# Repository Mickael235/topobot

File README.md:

# TopoBot

<p align="center">
  <strong>Autonomous holonomic robot for automated topographic surface-flatness inspection</strong><br>
  ENSIM × ESGT · 4th-year Engineering Project · 20252026
</p>

<p align="center">
  <strong>STM32 F446RE · Raspberry Pi · Mecanum · Encoders · AX-12 · XBee · KiCad · Python · C</strong>
</p>

---

## Project overview

**TopoBot** is a holonomic mobile robot developed to automate the repetitive part of a topographic surface-flatness survey.

In a conventional workflow, an operator manually moves a reflector from point to point while another operator operates the total station. TopoBot was designed to replace this manual point-by-point displacement with a configurable robotic mission:

1. define the measurement grid;
2. navigate to each waypoint;
3. deploy the topographic prism;
4. trigger / acquire the measurement;
5. recover the coordinates;
6. store and export the results.

The project combines **robotics, embedded control, electronics, radio communication, software supervision and topographic instrumentation** in one integrated prototype.

> **Project status:** the main hardware/software building blocks were integrated and validated on the prototype. Final industrial-grade accuracy, complete odometry/total-station fusion and a full production flatness campaign remain future work.

---

## Project at a glance

| Item | Implementation |
|---|---|
| Mobile base | Lynxmotion A4WD3 with 4 Mecanum wheels |
| Real-time controller | STM32 Nucleo F446RE |
| High-level computer | Raspberry Pi 4 |
| Motor power stage | 2 × Sabertooth motor drivers |
| Motion feedback | 4 incremental wheel encoders |
| Prism mechanism | AX-12 servomotor + rack-and-pinion mechanism |
| Station communication | XBee S2C radio link + serial / RS232 interface |
| Supervision | TopoBot Manager on tablet / browser |
| Data storage | SQLite on Raspberry Pi |
| Export | CSV |
| Real-time control loop | 100 Hz |
| Project budget | 500 |
| Actual project cost | 318.26 |
| Team | 4 engineering students |

### Design target

The functional specification targeted a configurable survey grid up to **50 m × 50 m**, with a nominal **0.5 m grid spacing** and a **40 mm spherical reflector**.

This is a **design requirement**, not a claim that the complete 50 × 50 m campaign was validated during the project.

---

# 1. Problem and mission

Manual surface inspection with a total station is repetitive: the reflector must be moved and positioned at many points, while measurements are triggered and recorded.

TopoBot aims to transform this workflow into a supervised autonomous sequence.

## Nominal survey cycle

```text
Define grid
    ?
Generate waypoints
    ?
Navigate to waypoint
    ?
Stabilize robot
    ?
Deploy prism
    ?
Trigger total-station measurement
    ?
Recover XYZ / angles / distance
    ?
Retract prism
    ?
Store point in SQLite
    ?
Send progress to TopoBot Manager
    ?
Next waypoint
    ?
Export mission data to CSV
```

The trajectory is generated as a **boustrophedon path**: the direction alternates from one grid row to the next to reduce unnecessary travel.

---

# 2. Functional architecture

The robot must interact with the surveyor, the surface, the total station, the energy source and the safety environment.

The main service functions are:

| Ref. | Function | Main requirement |
|---|---|---|
| FP1 | Move and orient the reflector | Configurable grid, 40 mm reflector |
| FC1 | Communicate with the total station | XBee S2C radio link, commands + coordinates |
| FC2 | Provide configuration and monitoring | Tablet / smartphone interface |
| FC3 | Provide energy autonomy | Rechargeable battery |
| FC4 | Operate in an indoor environment | Flat surface, future obstacle/drop detection |
| FC5 | Respect safety/environment constraints | Emergency stop and safe integration |

---

# 3. Robot structure

TopoBot is not a single-controller robot. It uses a **distributed architecture** in which the computational responsibilities are separated.

## Three control levels

```mermaid
flowchart LR
    UI["Tablet / Browser<br><b>TopoBot Manager</b>"]
    PI["Raspberry Pi 4<br><b>Mission supervisor / middleware</b>"]
    MCU["STM32 F446RE<br><b>Real-time motion controller</b>"]

    UI <-->|Network / Web interface| PI
    PI <-->|Binary serial protocol| MCU
```

### Level 1  Tablet / front-end

The operator uses TopoBot Manager to:

- connect to the robot;
- configure the survey area;
- choose the grid spacing;
- initialize the measurement mode;
- launch the mission;
- monitor progress;
- read logs and telemetry;
- stop the robot;
- export results.

### Level 2  Raspberry Pi / middleware

The Raspberry Pi acts as the high-level computer. It is responsible for:

- mission generation;
- waypoint sequencing;
- communication with the STM32;
- communication with the total station;
- measurement orchestration;
- SQLite data storage;
- WebSocket progress updates;
- CSV export;
- serving the supervision application.

### Level 3  STM32 / real-time control

The STM32 F446RE performs the time-critical functions:

- encoder acquisition;
- odometry;
- motion state machine;
- closed-loop motor control;
- Sabertooth command generation;
- emergency-stop handling;
- AX-12 prism control;
- execution of high-level motion orders.

This separation keeps real-time control local to the microcontroller while the Raspberry Pi focuses on supervision and mission logic.

---

# 4. Complete hardware architecture

```mermaid
flowchart TD
    APP["TopoBot Manager<br>Tablet / PC"]
    RPI["Raspberry Pi 4<br>Mission supervisor"]
    STM["STM32 F446RE<br>100 Hz real-time control"]
    PCB["Custom control board<br>KiCad / JLCPCB"]

    ENC["4 wheel encoders"]
    SAB["2 × Sabertooth<br>motor drivers"]
    MOT["4 DC motors<br>4 Mecanum wheels"]
    AX["AX-12 servo<br>Prism deployment"]
    ESTOP["Emergency stop"]
    BATT["Battery monitoring"]

    XB1["XBee S2C #1"]
    XB2["XBee S2C #2"]
    RS232["MAX3232 / RS232"]
    TOPCON["Robotic total station"]

    APP <-->|Supervision| RPI
    RPI <-->|Binary serial protocol| STM

    ENC --> STM
    STM --> PCB
    PCB --> SAB
    SAB --> MOT
    STM --> AX
    ESTOP --> PCB
    BATT --> PCB

    RPI <-->|USB / UART serial| XB1
    XB1 <-. "Radio" .-> XB2
    XB2 <-->|Serial| RS232
    RS232 <-->|RS232| TOPCON
```

---

# 5. Holonomic Mecanum platform

The Lynxmotion A4WD3 base uses four Mecanum wheels, allowing longitudinal, lateral and rotational motion.

## Wheel-direction combinations

| Motion | Front Left | Front Right | Rear Left | Rear Right |
|---|---:|---:|---:|---:|
| Forward | + | + | + | + |
| Backward | - | - | - | - |
| Left translation | - | + | + | - |
| Right translation | + | - | - | + |
| Left rotation | - | + | - | + |
| Right rotation | + | - | + | - |

The current survey mission mainly uses **translations with a constant orientation**. Nevertheless, the command interface preserves the full pose parameter:

```text
MOVE_TO(x, y, theta)
```

This keeps the architecture extensible toward complete pose control.

## Physical testing

Early tests demonstrated the expected Mecanum motion but also revealed parasitic rotation during straight translations due to wheel/motor asymmetry.

This led to:

- individual wheel testing;
- lower-speed validation;
- exploitation of encoder feedback;
- progressive closed-loop tuning.

---

# 6. STM32 real-time control

The embedded firmware is organised around several modules:

```text
STM32 firmware
+-- Mecanum kinematics
+-- Encoder acquisition
+-- Odometry
+-- PID / motion control
+-- Robot state machine
+-- Raspberry Pi protocol
+-- AX-12 prism control
+-- Safety / robot configuration
```

The repository contains the STM32 project in:

```text
firmware/stm32/
```

## Robot state machine

The controller uses the following main states:

```mermaid
stateDiagram-v2
    [*] --> IDLE
    IDLE --> MOVING: MOVE_TO
    MOVING --> SETTLING: target reached
    SETTLING --> DONE: position confirmed
    DONE --> IDLE
    MOVING --> ERROR: fault
    SETTLING --> ERROR: fault
    IDLE --> ESTOP: emergency stop
    MOVING --> ESTOP: emergency stop
    SETTLING --> ESTOP: emergency stop
```

Main states:

- `IDLE`  waiting for a command;
- `MOVING`  moving toward the target;
- `SETTLING`  stabilizing around the waypoint;
- `DONE`  waypoint reached and confirmed;
- `ERROR` / `ESTOP`  error or emergency stop.

The Raspberry Pi only sends the next waypoint after receiving a `DONE` status.

---

# 7. Raspberry Pi ? STM32 protocol

The Raspberry Pi does not directly control the motors.

It sends high-level commands to the STM32 using a lightweight binary protocol:

```text
[ START | CMD | LEN | PAYLOAD | CRC ]
```

The project uses a simple XOR-based CRC over the command, payload length and payload.

## Main commands

| Command | Role |
|---|---|
| `MOVE_TO` | Reach target pose `(x, y, ?)` |
| `STOP` | Immediate robot stop |
| `RESET_ODOM` | Reset odometry before a mission |
| `GET_STATUS` | Read position, speed and current state |
| `DEPLOY_PRISM` | Deploy the topographic prism |
| `RETRACT_PRISM` | Retract the prism |

The STM32 returns status frames such as:

```text
STATUS
DONE
ERROR
```

These messages allow the Raspberry Pi backend to orchestrate the mission without interfering with the real-time control loop.

---

# 8. Automatic mission logic

The mission is generated from:

```text
Zone width  = X
Zone length = Y
Grid step   = p
```

The backend generates the waypoint set:

```text
(xi, yj)
xi = i × p
yj = j × p
```

and orders them in a boustrophedon trajectory.

## Exact mission order

```text
1. RESET_ODOM
   +- Reset the robot local reference before starting.

2. Generate waypoints
   +- Build the complete boustrophedon measurement grid.

3. For each waypoint:
   +- Send MOVE_TO(x, y, ?)
   +- Wait for STM32 STATUS updates
   +- Continue only after DONE

4. If measurement mode is enabled:
   +- DEPLOY_PRISM
   +- Trigger / request Topcon measurement
   +- Recover measurement values
   +- RETRACT_PRISM

5. Save measurement
   +- Timestamp + local coordinates + station data ? SQLite

6. Notify front-end
   +- Mission progress and current data ? WebSocket

7. Continue with next waypoint

8. End mission
   +- Export the recorded dataset to CSV
```

A **station-independent test mode** was also kept. In this mode the robot can execute the grid with simulated measurement values, making it possible to debug navigation without depending on the topographic instrument.

---

# 9. Prism deployment mechanism

The topographic reflector is mounted on a rack-and-pinion mechanism actuated by an **AX-12 servomotor**.

The mechanism is responsible for:

```text
RETRACTED
    ?
DEPLOY_PRISM
    ?
Prism positioned for measurement
    ?
Total-station acquisition
    ?
RETRACT_PRISM
    ?
Robot resumes navigation
```

This sequence is synchronized with waypoint validation so that measurements are not requested while the robot is still moving.

---

# 10. Custom electronics

A custom control board was designed in **KiCad**, manufactured by **JLCPCB**, assembled and integrated into the robot.

The control electronics centralize:

- four encoder interfaces;
- STM32 connectivity;
- Sabertooth motor-control connections;
- AX-12 interface;
- emergency-stop circuitry;
- centralized power management;
- analog battery monitoring;
- expansion ports for future ultrasonic sensors.

The pre-existing power board was reused, while the **control board was redesigned specifically for this project**.

The KiCad project and Gerber manufacturing files are available under:

```text
hardware/control-board/
+-- kicad/
+-- manufacturing/
    +-- gerbers/
```

---

# 11. XBee radio link and total-station interface

TopoBot communicates with the robotic total station through a dedicated radio/serial chain.

## Communication chain

```text
Raspberry Pi
    ¦
    ¦ USB / UART serial
    ?
XBee S2C #1
    ))) RADIO (((
XBee S2C #2
    ¦
    ¦ Serial
    ?
MAX3232 / RS232 converter
    ¦
    ¦ RS232
    ?
Robotic total station
```

## XBee configuration used during the project

| Parameter | Configuration |
|---|---|
| Baud rate | 9600 |
| Data bits | 8 |
| Parity | None |
| Stop bits | 1 |
| Flow control | None |
| Channel | `C` / `0x0C` |
| PAN ID | `B332` |

The modules were configured using **Digi XCTU**.

## Total-station operating modes

The project explored three main station modes:

### Standard (`std`)
High-precision fixed measurement using fine targeting.

### Tracking (`trk`)
Fast tracking / targeting of a moving reflector.

### Continuous tracking
Continuous acquisition of distances and horizontal/vertical angles.

The automated acquisition sequence uses the station together with the robot prism workflow to recover the current measured point and feed it back into the mission data.

> **Known limitation:** the XBee radio link showed intermittent reliability problems during field testing. Improving the radio layer is one of the main future-work items.

---

# 12. TopoBot Manager

**TopoBot Manager** is the supervision interface designed for tablet use.

Its purpose is to hide the complexity of the robot, STM32, Raspberry Pi and total station behind a guided workflow.

The application follows three main user stages.

## 01  Connection

Before a mission starts, the interface verifies that the robot and measurement system are reachable.

Typical checks include:

- robot / Raspberry Pi connectivity;
- total-station link state;
- initialization readiness.

The operator cannot proceed until the system is ready.

## 02  Mission configuration

The operator defines:

- survey width `X`;
- survey length `Y`;
- measurement step `p`;
- measurement mode.

The backend uses these values to determine the grid and generate the mission waypoints.

## 03  Live mission supervision

During execution, the interface displays:

- mission progress;
- current point;
- 2D map of the grid;
- robot position;
- completed measurement points;
- activity/event log;
- latest measurement values;
- radio / system information;
- emergency-stop action.

---

# 13. Software communication layers

The complete information flow can be summarized as:

```text
+--------------------------------------+
¦ Tablet / Browser                    ¦
¦ TopoBot Manager                     ¦
¦ - configuration                     ¦
¦ - live map                          ¦
¦ - progress                          ¦
¦ - logs                              ¦
¦ - emergency stop                    ¦
+--------------------------------------+
                    ¦ HTTP / WebSocket
                    ?
+--------------------------------------+
¦ Raspberry Pi                        ¦
¦ Middleware / Mission Supervisor     ¦
¦ - route generation                  ¦
¦ - waypoint orchestration            ¦
¦ - SQLite                            ¦
¦ - CSV export                        ¦
¦ - total-station communication       ¦
+--------------------------------------+
                ¦               ¦
        Binary serial           ¦ XBee / serial
                ¦               ¦
                ?               ?
+----------------------+   +---------------------+
¦ STM32 F446RE         ¦   ¦ Robotic total      ¦
¦ - odometry           ¦   ¦ station            ¦
¦ - encoders           ¦   ¦ - measurement      ¦
¦ - PID                ¦   ¦ - tracking         ¦
¦ - motors             ¦   ¦ - XYZ / angles     ¦
¦ - AX-12              ¦   +---------------------+
+----------------------+
```

---

# 14. Data acquisition and export

Each measurement point is stored locally on the Raspberry Pi.

The project uses **SQLite** for mission data and exposes the final dataset through **CSV export**.

## Recorded fields

| Field | Meaning |
|---|---|
| `ID` | Unique measurement-point identifier |
| `HEURE` | Acquisition timestamp |
| `X`, `Y` | Local planar coordinates |
| `HZ` | Horizontal station angle |
| `V` | Vertical station angle |
| `DIST` | Radial distance measured by the station |

The mission data lifecycle is:

```text
Connection
    ?
Geometry configuration
    ?
Survey supervision
    ?
SQLite storage
    ?
CSV export
```

The CSV format was chosen to keep the results directly usable in spreadsheets and topographic post-processing tools.

---

# 15. Validation

The project was developed using progressive integration and physical tests.

## Tests performed

- individual motor-direction tests;
- Mecanum wheel-combination tests;
- forward/backward translation;
- lateral translation;
- encoder acquisition;
- odometry;
- Raspberry Pi ? STM32 communication;
- high-level `MOVE_TO` commands;
- robot state-machine behavior;
- AX-12 prism deployment/retraction;
- XBee radio communication;
- total-station operating modes;
- TopoBot Manager connection/configuration/live monitoring;
- mission generation and waypoint sequencing;
- station-independent simulated-measurement mode.

## Current validation status

| Subsystem | Status |
|---|---|
| Mecanum basic motion | ? Validated |
| STM32 real-time architecture | ? Implemented |
| Encoder feedback / odometry | ? Integrated |
| Raspberry Pi ? STM32 protocol | ? Implemented |
| High-level waypoint mission logic | ? Implemented |
| AX-12 prism deployment | ? Integrated and validated |
| Custom control PCB | ? Designed, manufactured and assembled |
| TopoBot Manager | ? Functional |
| Total-station communication modes | ? Exercised |
| XBee field robustness | ?? Functional but unreliable in some tests |
| Closed-loop tuning | ?? Requires finer adjustment |
| Odometry + total-station fusion | ?? Future work |
| Complete production flatness campaign | ?? Still to be finalized |

The goal of this repository is to present the **real engineering state of the prototype**, including both validated subsystems and remaining technical limitations.

---

# 16. Engineering challenges encountered

## Wheel synchronization

The first physical tests revealed unwanted rotation during straight movement.

Probable causes included:

- different mechanical behavior between motors;
- left/right timing asymmetry;
- open-loop control limitations.

Encoder feedback and closed-loop control were introduced to improve trajectory stability.

## Odometry drift

Wheel odometry accumulates errors when the wheels slip or the ground is irregular.

A future version should fuse:

```text
Wheel odometry
      +
High-precision total-station coordinates
      ?
Corrected robot localization
```

## Radio robustness

The XBee solution proved useful for prototyping but showed intermittent signal losses.

A more robust professional radio solution would be preferable for field deployment.

## Wiring reliability

The prototype contains a significant amount of point-to-point wiring. A future revision should use:

- locking connectors;
- improved cable routing;
- additional functions integrated directly onto the PCB.

## Active safety

Obstacle/drop sensors were planned in the architecture but were not fully operational in the final prototype.

---

# 17. My contribution

This was a **four-person team project** with distinct technical work packages.

My contribution focused primarily on **control, kinematics and motion validation**, including:

- development and validation of robot movement behavior;
- Mecanum motion testing;
- trajectory-execution testing;
- analysis of encoder feedback and positioning errors;
- participation in odometry / motion-control integration;
- contribution to waypoint and mission-motion logic;
- integration and testing of the AX-12 prism mechanism;
- physical prototype testing and debugging.

The complete project also includes major contributions from the other team members in supervision/UI, XBee communication and electronics/PCB integration.

---

# 18. Team organization

| Team member | Main work package |
|---|---|
| Bénéwindé Kontiebo | Project management · Supervision · HMI |
| Aymane Fariss | Communication · XBee / total-station link |
| Arsène Nguenang Youkap | Electronics · PCB · hardware integration |
| **Michael Essomba** | **Control · kinematics · AX-12 prism mechanism** |

The project was managed using an agile-inspired workflow with regular synchronization and milestone reviews.

---

# 19. Budget and reuse strategy

The project operated under a **500 budget**.

| Metric | Value |
|---|---:|
| Available budget | 500 |
| Actual project cost | **318.26** |
| Remaining budget | 181.74 |
| Budget utilization | ~64% |

A significant part of the platform was reused from previous cohorts:

- Lynxmotion chassis;
- DC motors;
- Mecanum wheels;
- Sabertooth drivers;
- XBee modules;
- AX-12 servo;
- prism mechanism;
- existing power board.

New spending focused mainly on the Raspberry Pi, STM32 boards, control electronics, passive components and PCB manufacturing.

---

# 20. Repository structure

```text
topobot/
+-- README.md
+-- .gitignore
¦
+-- assets/
¦   +-- images/
¦   ¦   +-- hero/
¦   ¦   ¦   +-- topobot-hero.png
¦   ¦   ¦
¦   ¦   +-- diagrams/
¦   ¦   ¦   +-- functional-architecture.png
¦   ¦   ¦   +-- mission-workflow.png
¦   ¦   ¦   +-- xbee-communication-chain.png
¦   ¦   ¦
¦   ¦   +-- hardware/
¦   ¦   ¦   +-- robot-platform.png
¦   ¦   ¦   +-- control-and-power-board.png
¦   ¦   ¦   +-- total-station.png
¦   ¦   ¦   +-- robot-cad-render.png
¦   ¦   ¦
¦   ¦   +-- ui/
¦   ¦       +-- topobot-manager-flow.png
¦   ¦       +-- mission-config.png
¦   ¦       +-- mission-live-dashboard.png
¦   ¦
¦   +-- video/
¦       +-- topobot-demo.mp4
¦
+-- docs/
¦   +-- presentation/
¦   +-- report/
¦   +-- technical/
¦
+-- firmware/
¦   +-- stm32/
¦
+-- hardware/
¦   +-- control-board/
¦       +-- kicad/
¦       +-- manufacturing/
¦           +-- gerbers/
¦
+-- software/
    +-- raspberry-pi/
    ¦   +-- tests/
    ¦
    +-- topobot-manager/
        +-- backend/
        +-- frontend/
```

Generated build files, local databases, virtual environments, IDE temporary files and dependency directories are intentionally excluded from version control.

---

# 21. Technologies

### Embedded systems

`C` · `STM32 F446RE` · `STM32CubeIDE` · `HAL`

### Robotics and control

`Mecanum kinematics` · `Encoders` · `Odometry` · `PID` · `State machine` · `AX-12`

### High-level software

`Python` · `Raspberry Pi` · `SQLite` · `WebSocket`

### Communication

`UART` · `Serial` · `XBee S2C` · `RS232`

### Electronics

`KiCad` · `PCB design` · `Gerber` · `JLCPCB`

### Instrumentation

`Robotic total station` · `Topographic prism` · `Tracking`

### Development

`Git` · `GitHub` · `Hardware testing` · `Technical documentation`

---

# 22. Demo

A short demonstration of the physical prototype is available here:

### [? Watch the TopoBot demo](assets/video/topobot-demo.mp4)

---

# 23. Documentation

Detailed engineering documentation is available in [`docs/`](docs/).

Main documents:

- [Final project report](docs/report/Rapport_final.pdf)
- [Project presentation](docs/presentation/TopoBot_Presentation.pdf)
- [STM32 firmware documentation](docs/technical/firmware/)
- [Hardware and wiring documentation](docs/technical/hardware/)
- [Raspberry Pi documentation](docs/technical/raspberry-pi/)
- [Testing documentation](docs/technical/tests/)
- [Odometry, PID and validation documentation](docs/technical/advanced/)

---

# 24. Future work

The next engineering priorities are:

1. **PID tuning**  
   Reduce oscillations and trajectory error.

2. **Odometry calibration**  
   Improve the estimation of `x`, `y` and `?`.

3. **Odometry / total-station sensor fusion**  
   Correct wheel-slip drift using high-precision station feedback.

4. **Radio reliability**  
   Replace or harden the XBee communication chain for field use.

5. **Active navigation safety**  
   Integrate obstacle, drop and stair detection.

6. **Wiring redesign**  
   Reduce point-to-point wiring and use locking connectors.

7. **Large-grid validation**  
   Validate longer missions and repeated surveys under realistic conditions.

8. **Full flatness campaign**  
   Complete the end-to-end autonomous survey and compare results against a reference workflow.

---

# 25. Project outcome

TopoBot evolved from an inherited mechanical platform into an integrated robotic prototype combining:

- a redesigned embedded architecture;
- STM32 real-time motion control;
- Raspberry Pi mission supervision;
- custom control electronics;
- Mecanum mobility;
- encoder odometry;
- AX-12 prism deployment;
- XBee / total-station communication;
- tablet-based mission supervision;
- local measurement storage and CSV export.

The project demonstrates the feasibility of automating a topographic surface-inspection workflow while also identifying the engineering work still required to reach robust field deployment.

---

# Project team

**ENSIM × ESGT  Le Mans University**  
Academic year: **20252026**

- Bénéwindé Kontiebo
- **Michael Essomba**
- Arsène Nguenang Youkap
- Aymane Fariss

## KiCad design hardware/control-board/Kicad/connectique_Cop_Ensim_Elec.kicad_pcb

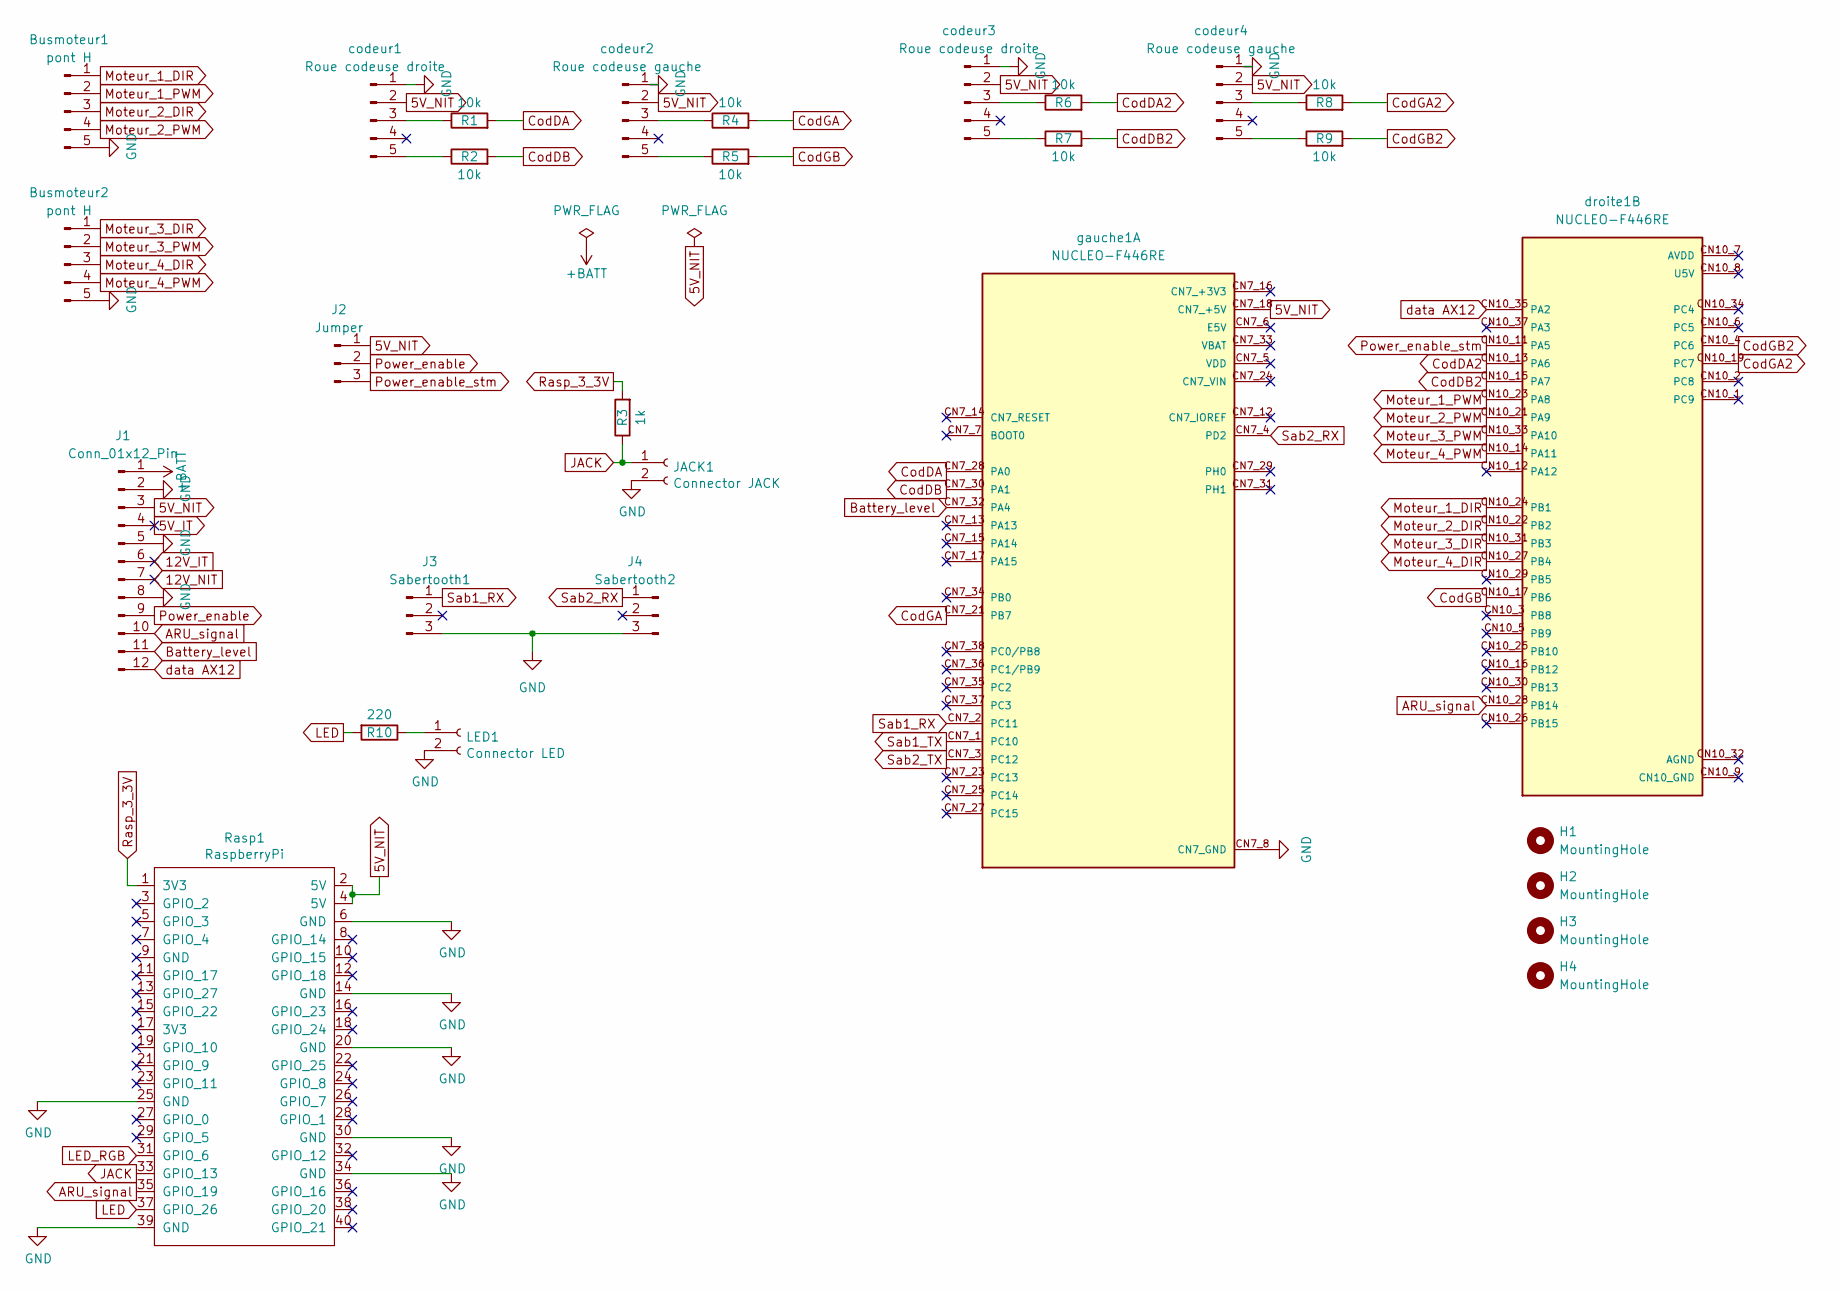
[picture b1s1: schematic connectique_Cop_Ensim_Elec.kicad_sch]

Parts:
Busmoteur1, Busmoteur2: pont H; JST_PH_B5B-PH-K_1x05_P2.00mm_Vertical
H1, H2, H3, H4: MountingHole; MountingHole_3.2mm_M3_DIN965_Pad
J1: Conn_01x12_Pin; PinHeader_1x12_P2.54mm_Vertical
J2: Jumper; PinHeader_1x03_P2.54mm_Vertical
J3: Sabertooth1; JST_PH_B3B-PH-K_1x03_P2.00mm_Vertical
J4: Sabertooth2; JST_PH_B3B-PH-K_1x03_P2.00mm_Vertical
JACK1: Connector JACK; JST_PH_B2B-PH-K_1x02_P2.00mm_Vertical
LED1: Connector LED; JST_PH_B2B-PH-K_1x02_P2.00mm_Vertical
R1, R2, R4, R5, R6, R7, R8, R9: 10k; R_Axial_DIN0207_L6.3mm_D2.5mm_P10.16mm_Horizontal
R3: 1k; R_Axial_DIN0207_L6.3mm_D2.5mm_P10.16mm_Horizontal
R10: 220; R_Axial_DIN0207_L6.3mm_D2.5mm_P10.16mm_Horizontal
Rasp1: RaspberryPi; MODULE_RASPBERRY_PI_4B_4GB
codeur1, codeur3: Roue codeuse droite; JST_PH_B5B-PH-K_1x05_P2.00mm_Vertical
codeur2, codeur4: Roue codeuse gauche; JST_PH_B5B-PH-K_1x05_P2.00mm_Vertical
droite1: NUCLEO-F446RE; MODULE_NUCLEO-F446RE droite; PARTREV 13; DigiKey_Part_Number 497-15882-ND
gauche1: NUCLEO-F446RE; MODULE_NUCLEO-F446RE gauche; PARTREV 13; DigiKey_Part_Number 497-15882-ND

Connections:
5V_IT: J1.4
5V_NIT: J1.3, J2.1, Rasp1.2 (5V), Rasp1.4 (5V), codeur1.2, codeur2.2, codeur3.2, codeur4.2, gauche1.CN7_18 (CN7_+5V)
12V_IT: J1.6
12V_NIT: J1.7
+BATT: J1.1
ARU_signal: J1.10, Rasp1.35 (GPIO_19), droite1.CN10_28 (PB14)
Battery_level: J1.11, gauche1.CN7_32 (PA4)
CodDA: R1.2, gauche1.CN7_28 (PA0)
CodDA2: R6.2, droite1.CN10_13 (PA6)
CodDB: R2.2, gauche1.CN7_30 (PA1)
CodDB2: R7.2, droite1.CN10_15 (PA7)
CodGA: R4.2, gauche1.CN7_21 (PB7)
CodGA2: R8.2, droite1.CN10_19 (PC7)
CodGB: R5.2, droite1.CN10_17 (PB6)
CodGB2: R9.2, droite1.CN10_4 (PC6)
GND: Busmoteur1.5, Busmoteur2.5, J1.2, J1.5, J1.8, J3.3, J4.3, JACK1.2, LED1.2, Rasp1.6 (GND), Rasp1.14 (GND), Rasp1.20 (GND), Rasp1.25 (GND), Rasp1.30 (GND), Rasp1.34 (GND), Rasp1.39 (GND), codeur1.1, codeur2.1, codeur3.1, codeur4.1, gauche1.CN7_8 (CN7_GND), gauche1.CN7_19 (CN7_GND), gauche1.CN7_20 (CN7_GND), gauche1.CN7_22 (CN7_GND)
JACK: JACK1.1, R3.1, Rasp1.33 (GPIO_13)
LED: R10.2, Rasp1.37 (GPIO_26)
LED_RGB: Rasp1.31 (GPIO_6)
Moteur_1_DIR: Busmoteur1.1, droite1.CN10_24 (PB1)
Moteur_1_PWM: Busmoteur1.2, droite1.CN10_23 (PA8)
Moteur_2_DIR: Busmoteur1.3, droite1.CN10_22 (PB2)
Moteur_2_PWM: Busmoteur1.4, droite1.CN10_21 (PA9)
Moteur_3_DIR: Busmoteur2.1, droite1.CN10_31 (PB3)
Moteur_3_PWM: Busmoteur2.2, droite1.CN10_33 (PA10)
Moteur_4_DIR: Busmoteur2.3, droite1.CN10_27 (PB4)
Moteur_4_PWM: Busmoteur2.4, droite1.CN10_14 (PA11)
unnamed: LED1.1, R10.1
unnamed: R1.1, codeur1.3
unnamed: R2.1, codeur1.5
unnamed: R4.1, codeur2.3
unnamed: R5.1, codeur2.5
unnamed: R6.1, codeur3.3
unnamed: R7.1, codeur3.5
unnamed: R8.1, codeur4.3
unnamed: R9.1, codeur4.5
Power_enable: J1.9, J2.2
Power_enable_stm: J2.3, droite1.CN10_11 (PA5)
Rasp_3_3V: R3.2, Rasp1.1 (3V3)
Sab1_RX: J3.1, gauche1.CN7_2 (PC11)
Sab1_TX: gauche1.CN7_1 (PC10)
Sab2_RX: J4.1, gauche1.CN7_4 (PD2)
Sab2_TX: gauche1.CN7_3 (PC12)
data AX12: J1.12, droite1.CN10_35 (PA2)

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
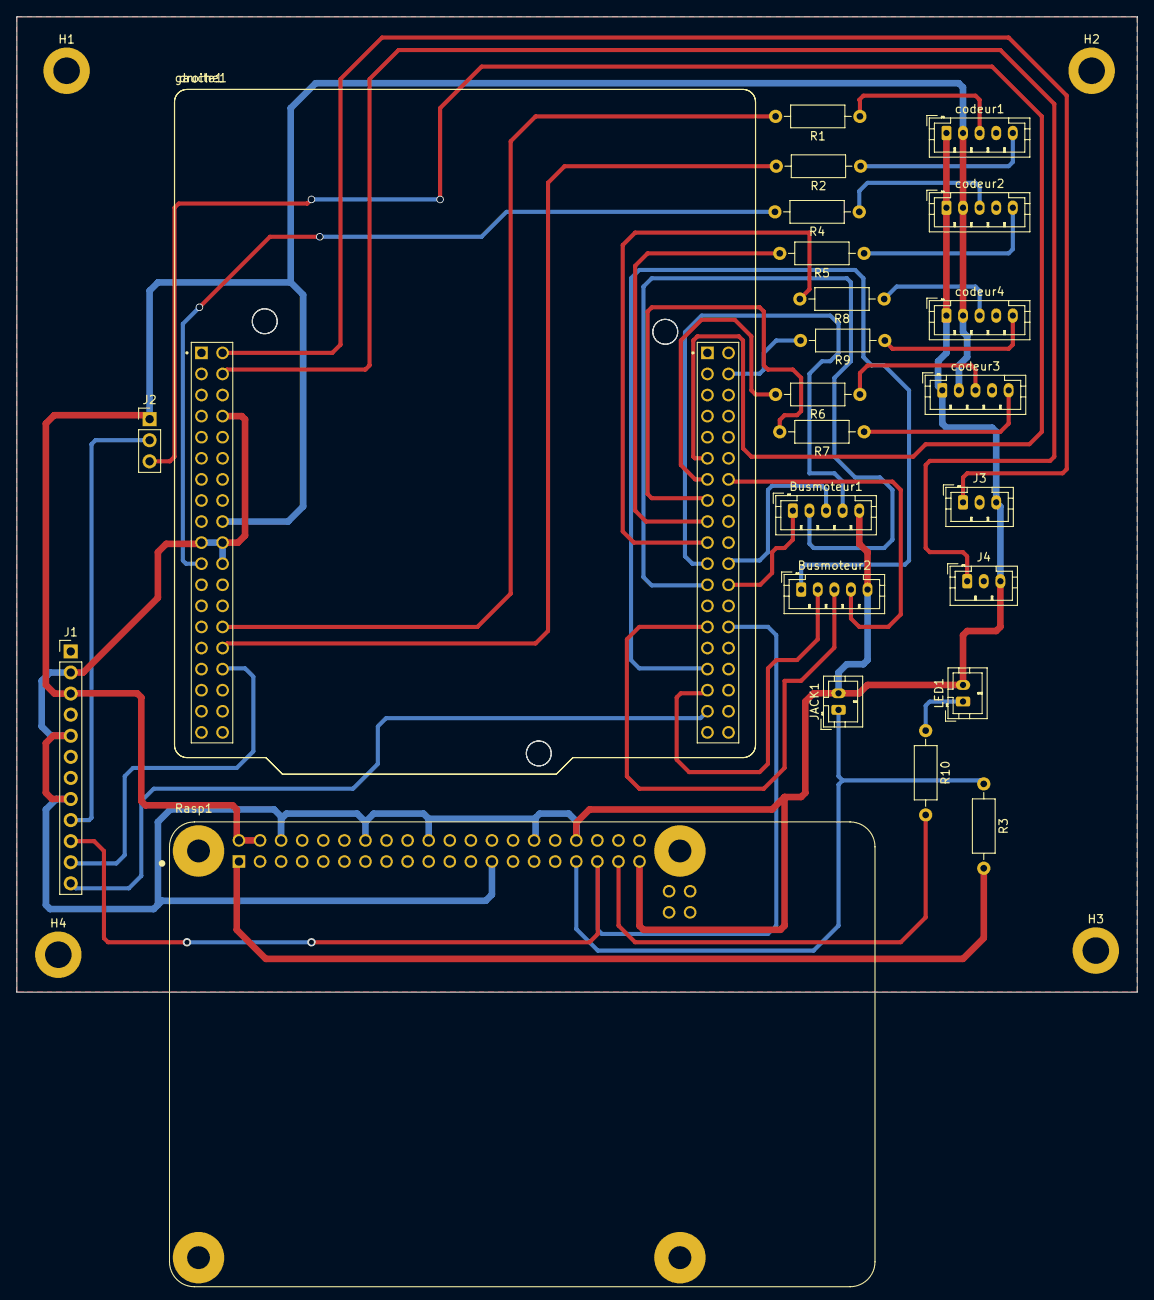
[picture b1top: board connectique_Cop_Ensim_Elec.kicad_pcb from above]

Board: 2 copper layers, 135.0 x 117.5 mm, 29 parts (0 on the bottom side), 37 nets.

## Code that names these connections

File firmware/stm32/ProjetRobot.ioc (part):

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Mcu.Name=STM32F446R(C-E)Tx
Mcu.Package=LQFP64
Mcu.UserName=STM32F446RETx
PA0-WKUP.GPIOParameters=GPIO_Label
PA0-WKUP.GPIO_Label=CodDA
PA0-WKUP.Signal=S_TIM2_CH1_ETR
PA1.GPIOParameters=GPIO_Label
PA1.GPIO_Label=CodDB
PA1.Signal=S_TIM2_CH2
PA10.GPIOParameters=GPIO_Label
PA10.GPIO_Label=Moteur_3_PWM
PA10.Signal=S_TIM1_CH3
PA11.GPIOParameters=GPIO_Label
PA11.GPIO_Label=Moteur_4_PWM
PA11.Signal=S_TIM1_CH4
PA13.Mode=Serial_Wire
PA13.Signal=SYS_JTMS-SWDIO
PA14.Mode=Serial_Wire
PA14.Signal=SYS_JTCK-SWCLK
PA2.GPIOParameters=GPIO_Label
PA2.GPIO_Label=data_AX12
PA2.Mode=Asynchronous
PA2.Signal=USART2_TX
PA3.Mode=Asynchronous
PA3.Signal=USART2_RX
PA4.GPIOParameters=GPIO_Label
PA4.GPIO_Label=Battery_level
PA4.Signal=ADCx_IN4
PA5.GPIOParameters=GPIO_Label
PA5.GPIO_Label=Power_enable_stm
PA5.Signal=GPIO_Output
PA6.GPIOParameters=GPIO_Label
PA6.GPIO_Label=CodDA2
PA6.Signal=S_TIM3_CH1
PA7.GPIOParameters=GPIO_Label
PA7.GPIO_Label=CodDB2
PA7.Signal=S_TIM3_CH2
PA8.GPIOParameters=GPIO_Label
PA8.GPIO_Label=Moteur_1_PWM
PA8.Signal=S_TIM1_CH1
PA9.GPIOParameters=GPIO_Label
PA9.GPIO_Label=Moteur_2_PWM
PA9.Signal=S_TIM1_CH2
PB1.GPIOParameters=GPIO_Label
PB1.GPIO_Label=Moteur_1_DIR
PB1.Signal=GPIO_Output
PB14.GPIOParameters=GPIO_PuPd,GPIO_Label
PB14.GPIO_Label=ARU_signal
PB14.GPIO_PuPd=GPIO_PULLUP
PB14.Signal=GPIO_Input
PB2.GPIOParameters=GPIO_Label
PB2.GPIO_Label=Moteur_2_DIR
PB2.Signal=GPIO_Output
PB3.GPIOParameters=GPIO_Label
PB3.GPIO_Label=Moteur_3_DIR
PB3.Signal=GPIO_Output
PB4.GPIOParameters=GPIO_Label
PB4.GPIO_Label=Moteur_4_DIR
PB4.Signal=GPIO_Output
PB6.GPIOParameters=GPIO_Label
PB6.GPIO_Label=CodGB
PB6.Signal=S_TIM4_CH1
PB7.GPIOParameters=GPIO_Label
PB7.GPIO_Label=CodGA
PB7.Signal=S_TIM4_CH2
PC10.GPIOParameters=GPIO_Label
PC10.GPIO_Label=Sabertooth1_TX
PC10.Mode=Asynchronous
PC10.Signal=UART4_TX
PC11.GPIOParameters=GPIO_Label
PC11.GPIO_Label=Sabertooth1_RX
PC11.Mode=Asynchronous
PC11.Signal=UART4_RX
PC12.GPIOParameters=GPIO_Label
PC12.GPIO_Label=Sabertooth2_TX
PC12.Mode=Asynchronous
PC12.Signal=UART5_TX
PC6.GPIOParameters=GPIO_Label
PC6.GPIO_Label=CodG2B
PC6.Signal=S_TIM8_CH1
PC7.GPIOParameters=GPIO_Label
PC7.GPIO_Label=CodGA2
PC7.Signal=S_TIM8_CH2
PD2.GPIOParameters=GPIO_Label
PD2.GPIO_Label=Sabertooth2_RX
PD2.Mode=Asynchronous
PD2.Signal=UART5_RX
PH0-OSC_IN.Mode=HSE-External-Oscillator
PH0-OSC_IN.Signal=RCC_OSC_IN
PH1-OSC_OUT.Mode=HSE-External-Oscillator
PH1-OSC_OUT.Signal=RCC_OSC_OUT
RCC.HSE_VALUE=8000000
RCC.SYSCLKFreq_VALUE=84000000
RCC.SYSCLKSource=RCC_SYSCLKSOURCE_PLLCLK
board=NUCLEO-F446RE
boardIOC=true
